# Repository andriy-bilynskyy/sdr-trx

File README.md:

# SDR transceiver

## General info

- [SDR wiki](https://en.wikipedia.org/wiki/Software-defined_radio)
- [Quadrature Mixers, IQ Demodulation, and the Tayloe Detector](https://www.youtube.com/watch?v=JuuKF1RFvBM)
- [A Software-Defined Radio for the Masses, Part 1](https://www.arrl.org/files/file/Technology/tis/info/pdf/020708qex013.pdf)
- [Hardware Implementation of Software Radio Receivers](https://www.ripublication.com/irph/ijeee_spl/ijeeev7n4_08.pdf)

## Main concept

- Fully open source design include HW and SW
- Only free development SW
- Single board design to keep design simple
- SMT design
- Standalone battery powered device

## Folder structure

- **schematic/** - KiCad PCB design. Schematic, PCB routing, manufacture documentation.
- **simulation/** - HW components spice simulations.
- **firmware/** - firmware.
- **calculations/** - calculations and considerations needed for HW/SW design implementation.
- **datasheets/** - datasheets used during design implementations.
- **tests/** - projects to check design components functionality.

## Block diagram

See schematic/sdr-trx/sdr-trx.sch which is top level schematic.

## Great thanks for sharing their approaches knowledges and considerations

- M0NKA http://www.m0nka.co.uk/ - Small and inexpensive homebrew HF radio.
- https://www.flexradio.com/ - RF transceivers.
- https://elecraft.com/products/kx3-all-mode-160-6-m-transceiver - SDR transceiver.
- IN3OTD https://www.qsl.net/in3otd/index.html - lot of very useful information information and approaches. RF PA got from this site.
- https://ludens.cl/Electron/Electron.html - Here's the best explanation of common mistake in push-pull RF PA transformers design I've ever seen. See https://ludens.cl/Electron/mosfetamps/amps.html.
- https://www.youtube.com/watch?v=byF1FLdbUiA - Simple and understandable explanation of a directional coupler.
- https://rf-tools.com/lc-filter/ - Perfect on-line filter calculator.

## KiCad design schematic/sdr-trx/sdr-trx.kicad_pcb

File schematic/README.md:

# SDR transceiver schematic

## Folder structure

- **sdr-trx/** - KiCad PCB project, [KiCad](https://kicad-pcb.org/).  The folder contains schematics and PCB routing. Used KiCad version 5.1.5. Standard KiCad libraries are involved, so please check your version if you have troubles with standard components.
- **mcu-pinout.ioc** - STM32 MCU pinout. [STM32CubeMX](https://www.st.com/en/development-tools/stm32cubemx.html). Used version 5.6.1.
- **pa-transformer.odg** - RF power amplifier push-pull transformer winding. LibreOffice Draw document. Used version 6.4.3.2.
- **swr-transformer.odg** - SWR meter transformer winding. LibreOffice Draw document. Used version 6.4.3.2.
- **doc/** - generated schematic/PCB documentation extracted from KiCad. Folder containing manufacturing documents. [PCB Manufacturing](https://www.elecrow.com/pcb-manufacturing.html)

## Main features

- Single board design, size 239 x 145 mm.
- Only SMD components are used. Avoid using components with pins under package (BGA, QFN, PLCC) due difficulties during hand soldering. Same situation with components with huge pins count.
- Avoid manual inductors/transformer winding. Only two components need manual winding (PA transformer and SWR meter directional coupler).
- Four sides PCB for better EMI. Shield for low power RF part to avoid influence from MCU and UI digital part.
- No chassis mounted components to avoid using wired connections which are not reliable at lest during development stage.
- Switching DC-DC are not used to decrease their EMI on RF part.
- Reduced mechanical buttons due to using capacitive touchscreen.
- On-board Li-batteries. Batteries protection and cell balancing are used.
- Flexible power management. MCU controls powering of RF circuit.
- Covers all HF bands 1.8 - 30 MHz.
- 5W RF power amplifies. Compromise between PCB size and transmitted power. MCU controls the temperature of output RF LDMOS transistors. Output power is also MCU controlled.
- On-board SWR meter. Specialized detector IC is used to increase accuracy.
- Input power supply and ESD protection on inputs.
- Low harmonic distortion due to direct conversion and 2 stages filtration (5-th order Chebyshev BPF after modulator and 7-th order Elliptic LPF after power amplifier).
- Low noise RF-receiver.
- On-board audio amplifier to use cheap headsets for PC.
- USB OTG and SD card interface.

## Known HW issues rev v1.0

See doc/hw_issues.odt

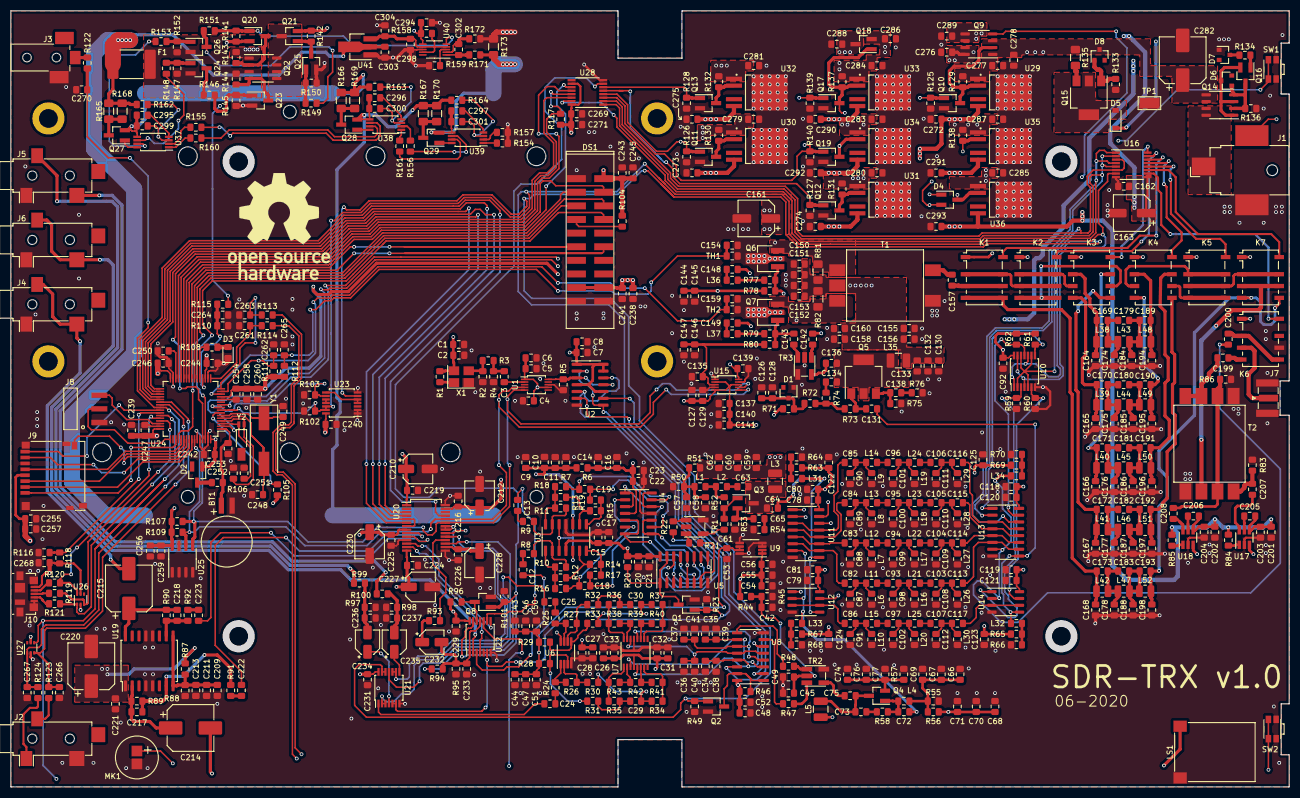
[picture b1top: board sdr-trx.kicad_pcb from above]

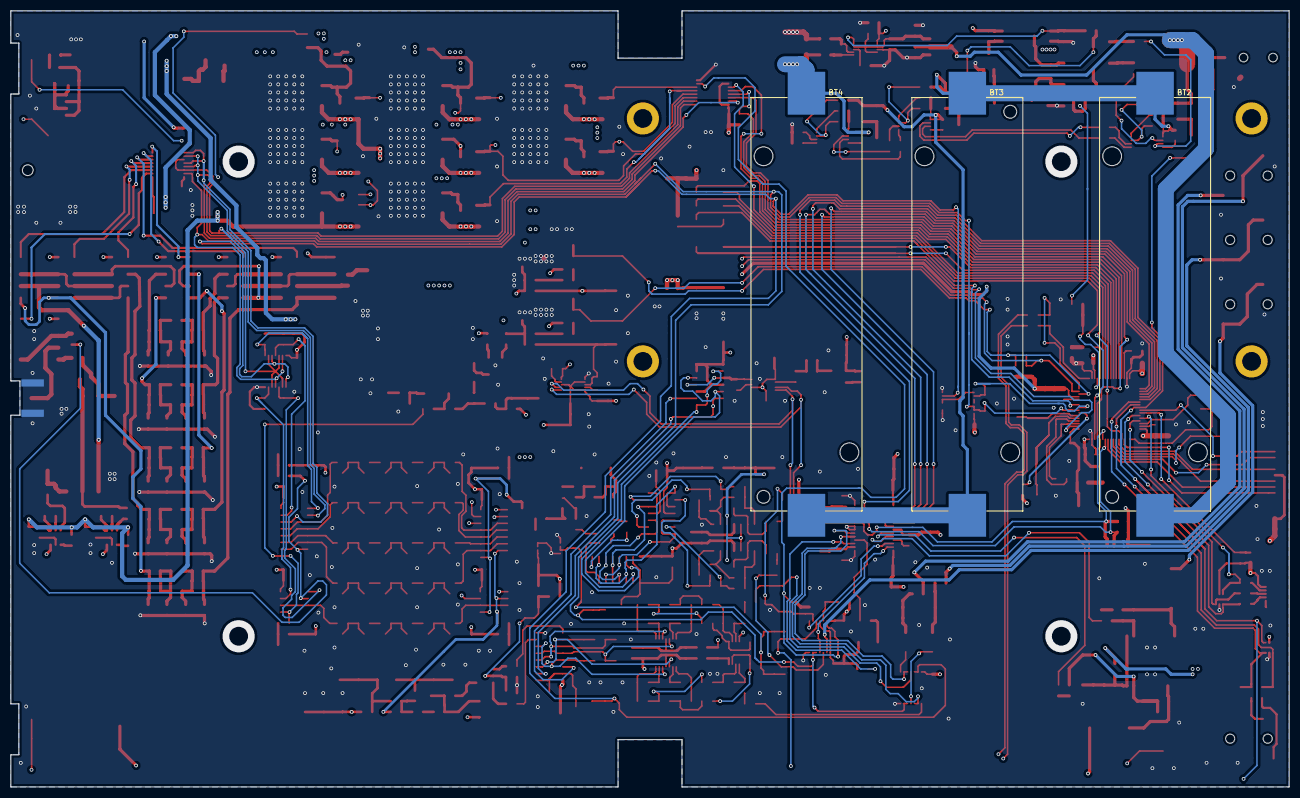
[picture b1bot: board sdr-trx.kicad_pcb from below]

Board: 4 copper layers, 238.4 x 144.7 mm, 645 parts (3 on the bottom side), 372 nets.

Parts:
BT1: ML-920S; ML920S
BT2, BT3, BT4: 18650-holder-1042; BATT-18650-1042
C1, C3, C4, C5, C8, C10, C15, C16, C20, C22, C27, C32, C45, C46, C47, C48, C56, C57, C59, C61, C63, C64, C65, C66, C68, C72, C73, C74, C75, C80, C81, C82, C83, C84, C85, C86, C92, C113, C114, C115, C116, C117, C118, C119, C122, C123, C124, C125, C128, C129, C131, C132, C134, C135, C136, C138, C139, C140, C142, C143, C144, C146, C148, C149, C150, C151, C152, C153, C154, C157, C159, C199, C200, C201, C202, C205, C206, C207, C208, C211, C216, C219, C221, C224, C225, C226, C229, C231, C240, C241, C243, C244, C246, C247, C253, C255, C258, C259, C261, C262, C263, C264, C265, C269, C277, C278, C279, C280, C281, C283, C284, C285, C286, C287, C298, C299, C300, C301, C302, C303, C304: 0.1uF; C_0805_2012Metric_Pad1.15x1.40mm_HandSolder
C2, C7, C11, C14, C21, C28, C33, C49, C50, C51, C52, C54, C58, C60, C67, C70, C76, C78, C79, C120, C121, C133, C137, C145, C147, C203, C204, C213, C254, C294, C295, C296, C297: 10nF; C_0805_2012Metric_Pad1.15x1.40mm_HandSolder
C6, C9, C12, C13, C17, C23, C24, C25, C26, C31, C42, C43, C44, C53, C55, C126, C127, C130, C141, C155, C156, C158, C160, C162, C209, C222, C223, C242: 1.0uF; C_0805_2012Metric_Pad1.15x1.40mm_HandSolder
C18, C19, C29, C30, C38, C39, C40, C41: 8.2nF 1%; C_0805_2012Metric_Pad1.15x1.40mm_HandSolder
C34, C35, C36, C37: N/A; C_0805_2012Metric_Pad1.15x1.40mm_HandSolder
C62, C69, C71, C77, C89, C110, C179, C194, C217, C218, C266, C267, C270: 1.0nF; C_0805_2012Metric_Pad1.15x1.40mm_HandSolder
C87: 3.3nF; C_0805_2012Metric_Pad1.15x1.40mm_HandSolder
C88, C109, C174: 1.8nF; C_0805_2012Metric_Pad1.15x1.40mm_HandSolder
C90, C111, C195: 560pF; C_0805_2012Metric_Pad1.15x1.40mm_HandSolder
C91, C112: 300pF; C_0805_2012Metric_Pad1.15x1.40mm_HandSolder
C93, C103, C180: 620pF; C_0805_2012Metric_Pad1.15x1.40mm_HandSolder
C94, C104, C196: 330pF; C_0805_2012Metric_Pad1.15x1.40mm_HandSolder
C95, C105, C182: 200pF; C_0805_2012Metric_Pad1.15x1.40mm_HandSolder
C96, C106, C183: 91pF; C_0805_2012Metric_Pad1.15x1.40mm_HandSolder
C97, C107: 62pF; C_0805_2012Metric_Pad1.15x1.40mm_HandSolder
C98: 4.7nF; C_0805_2012Metric_Pad1.15x1.40mm_HandSolder
C99: 2.7nF; C_0805_2012Metric_Pad1.15x1.40mm_HandSolder
C100: 1.5nF; C_0805_2012Metric_Pad1.15x1.40mm_HandSolder
C101, C175: 910pF; C_0805_2012Metric_Pad1.15x1.40mm_HandSolder
C102, C176: 510pF; C_0805_2012Metric_Pad1.15x1.40mm_HandSolder
C108: 3.0nF; C_0805_2012Metric_Pad1.15x1.40mm_HandSolder
C161, C163: 47uF 16V; CP_Elec_6.3x5.8
C164: 1.6nF; C_0805_2012Metric_Pad1.15x1.40mm_HandSolder
C165, C185, C189: 750pF; C_0805_2012Metric_Pad1.15x1.40mm_HandSolder
C166, C186, C190: 430pF; C_0805_2012Metric_Pad1.15x1.40mm_HandSolder
C167, C187, C191: 240pF; C_0805_2012Metric_Pad1.15x1.40mm_HandSolder
C168: 130pF; C_0805_2012Metric_Pad1.15x1.40mm_HandSolder
C169, C233, C236, C237: 220pF; C_0805_2012Metric_Pad1.15x1.40mm_HandSolder
C170: 120pF; C_0805_2012Metric_Pad1.15x1.40mm_HandSolder
C171, C193: 68pF; C_0805_2012Metric_Pad1.15x1.40mm_HandSolder
C172: 39pF; C_0805_2012Metric_Pad1.15x1.40mm_HandSolder
C173: 18pF; C_0805_2012Metric_Pad1.15x1.40mm_HandSolder
C177: 270pF; C_0805_2012Metric_Pad1.15x1.40mm_HandSolder
C178, C192: 160pF; C_0805_2012Metric_Pad1.15x1.40mm_HandSolder
C181: 360pF; C_0805_2012Metric_Pad1.15x1.40mm_HandSolder
C184: 1.3nF; C_0805_2012Metric_Pad1.15x1.40mm_HandSolder
C188: 150pF; C_0805_2012Metric_Pad1.15x1.40mm_HandSolder
C197: 180pF; C_0805_2012Metric_Pad1.15x1.40mm_HandSolder
C198: 110pF; C_0805_2012Metric_Pad1.15x1.40mm_HandSolder
C210, C212, C227, C228, C230: 10uF 35V; CP_Elec_5x5.8
C214, C215, C220, C282: 330uF 16V; CP_Elec_8x10.5
C232, C234, C235: 1.0uF 50V; CP_Elec_4x5.4
C238, C239, C245, C250, C256, C257, C260, C268, C271, C272, C273, C274, C275, C276, C288, C289, C290, C291, C292, C293: 4.7uF; C_0805_2012Metric_Pad1.15x1.40mm_HandSolder
C248, C249, C251, C252: 22pF; C_0805_2012Metric_Pad1.15x1.40mm_HandSolder
D1: BZX84-C4V7; D_SOT-23_ANK
D2: BAT54W; SOT-23_Handsoldering
D3: 150080RS75000; D_0805_2012Metric_Pad1.15x1.40mm_HandSolder
D4: BAT54AW; SOT-23_Handsoldering
D5: PMEG2010ER; D_SOD-123
D6, D7: BZX84-C12; D_SOT-23_ANK
D8: BZX84-C2V4; D_SOT-23_ANK
DS1: NHD-4.3-480272FT-CTXL-CTP
F1: ASMDC300F/24; Fuse_2920_7451Metric_Pad2.10x5.45mm_HandSolder
J1: PJ-036AH-SMT; BarrelJack_CUI_PJ-036AH-SMT_Horizontal
J2: SJ-3524-SMT-TR; Jack_3.5mm_CUI_SJ-3524-SMT_Horizontal
J3: PJ1-022-SMT
J4: SJ-3524-SMT-TR-GR; Jack_3.5mm_CUI_SJ-3524-SMT_Horizontal
J5: SJ-3524-SMT-TR-BE; Jack_3.5mm_CUI_SJ-3524-SMT_Horizontal
J6: SJ-3524-SMT-TR-PI; Jack_3.5mm_CUI_SJ-3524-SMT_Horizontal
J7: CON-SMA-EDGE; SMA_Samtec_SMA-J-P-X-ST-EM1_EdgeMount
J8: TSM-103-02
J9: DM3D-SF; microSD_HC_Hirose_DM3D-SF
J10: 47346-0001; USB_Micro-B_Molex_47346-0001
K1, K2, K3, K4, K5, K6, K7: AGQ200A12; Relay_DPDT_Omron_G6K-2F-Y
L1, L4, L31, L32, L33, L34: MLZ2012N101LT000; L_0805_2012Metric_Pad1.15x1.40mm_HandSolder
L2: MLF2012DR22; L_0805_2012Metric_Pad1.15x1.40mm_HandSolder
L3, L5, L35: LQW32FT470M0HL; L_1210_3225Metric_Pad1.42x2.65mm_HandSolder
L6, L14, L24, L26: MLF2012A1R5; L_0805_2012Metric_Pad1.15x1.40mm_HandSolder
L7, L15, L25, L27: MLF2012DR82; L_0805_2012Metric_Pad1.15x1.40mm_HandSolder
L8, L28: MLF2012DR47; L_0805_2012Metric_Pad1.15x1.40mm_HandSolder
L9, L29: MLF2012DR27; L_0805_2012Metric_Pad1.15x1.40mm_HandSolder
L10, L30: MLF2012DR15; L_0805_2012Metric_Pad1.15x1.40mm_HandSolder
L11, L21: MLF2012E6R8; L_0805_2012Metric_Pad1.15x1.40mm_HandSolder
L12, L22: MLF2012A3R9; L_0805_2012Metric_Pad1.15x1.40mm_HandSolder
L13, L23: MLF2012A2R2; L_0805_2012Metric_Pad1.15x1.40mm_HandSolder
L16, L36, L37: MLF2012A1R0; L_0805_2012Metric_Pad1.15x1.40mm_HandSolder
L17: MLF2012DR56; L_0805_2012Metric_Pad1.15x1.40mm_HandSolder
L18: MLF2012DR33; L_0805_2012Metric_Pad1.15x1.40mm_HandSolder
L19: MLF2012DR18; L_0805_2012Metric_Pad1.15x1.40mm_HandSolder
L20: MLF2012DR10; L_0805_2012Metric_Pad1.15x1.40mm_HandSolder
L38: 744758327A; L_1008_2520Metric
L39: 744758315A; L_1008_2520Metric
L40, L44: 744758310A; L_1008_2520Metric
L41, L45: 744758256A; L_1008_2520Metric
L42, L46, L51: 744762233A; L_1008_2520Metric
L43, L48: 744758318A; L_1008_2520Metric
L47, L52: 744762222A; L_1008_2520Metric
L49: 744758312A; L_1008_2520Metric
L50: 744758268A; L_1008_2520Metric
LS1: CMS-15113-078SP; CMS-15113-078S
MK1: DOM-3027L-HD-R
Q1, Q2, Q8, Q10, Q11, Q12, Q13, Q17, Q19, Q27, Q28, Q29: BSS138P; SOT-23_Handsoldering
Q3: MMBT2222A; SOT-23_Handsoldering
Q4: BFU520W; SOT-23_Handsoldering
Q5: DZT2222A; SOT-223-3_TabPin2
Q6, Q7: PD85004; SOT-89-3_Handsoldering
Q9, Q14, Q22: Si4909DY; SO-8_3.9x4.9mm_P1.27mm
Q15: BCP52; SOT-223-3_TabPin2
Q16, Q24, Q26: 2SB1198K; SOT-23_Handsoldering
Q18, Q21: DMP3099L; SOT-23_Handsoldering
Q20, Q23, Q25: 2SC2412K; SOT-23_Handsoldering
R1, R20, R46, R59, R60, R61, R62, R63, R64, R65, R66, R67, R68, R69, R70, R84, R85, R96, R134, R136: 10K; R_0805_2012Metric_Pad1.15x1.40mm_HandSolder
R2, R4, R21, R22: 100R; R_0805_2012Metric_Pad1.15x1.40mm_HandSolder
R3, R83, R86: 68R; R_0805_2012Metric_Pad1.15x1.40mm_HandSolder
R5: 51R; R_0805_2012Metric_Pad1.15x1.40mm_HandSolder
R6, R7, R26, R27, R28, R29, R38, R40, R41, R43, R44, R45, R87, R88: 1K 1%; R_0805_2012Metric_Pad1.15x1.40mm_HandSolder
R8, R9, R10, R11, R12, R13, R14, R15, R110, R111, R112: 10K 1%; R_0805_2012Metric_Pad1.15x1.40mm_HandSolder
R16, R17, R18, R19, R34, R35, R36, R37, R47, R48: 100R 1%; R_0805_2012Metric_Pad1.15x1.40mm_HandSolder
R23, R49, R95, R101, R102, R103, R104, R105, R117, R118, R125, R126, R127, R128, R139, R140: 47K; R_0805_2012Metric_Pad1.15x1.40mm_HandSolder
R24, R25, R76, R119, R120, R121, R122, R123, R124: 22R; R_0805_2012Metric_Pad1.15x1.40mm_HandSolder
R30, R31, R32, R33: 820R 1%; R_0805_2012Metric_Pad1.15x1.40mm_HandSolder
R39, R42: 10R 1%; R_0805_2012Metric_Pad1.15x1.40mm_HandSolder
R50, R55, R94: 2.2K; R_0805_2012Metric_Pad1.15x1.40mm_HandSolder
R51, R71, R78, R80: 1.8K; R_0805_2012Metric_Pad1.15x1.40mm_HandSolder
R52: 180R; R_0805_2012Metric_Pad1.15x1.40mm_HandSolder
R53, R75: 47R; R_0805_2012Metric_Pad1.15x1.40mm_HandSolder
R54: 18R; R_0805_2012Metric_Pad1.15x1.40mm_HandSolder
R56, R91, R92, R97, R98, R99, R100, R129, R130, R131, R132, R133, R137, R138: 4.3K; R_0805_2012Metric_Pad1.15x1.40mm_HandSolder
R57: 150R; R_0805_2012Metric_Pad1.15x1.40mm_HandSolder
R58, R162, R163, R164, R171, R172: 470R; R_0805_2012Metric_Pad1.15x1.40mm_HandSolder
R72: 15K; R_0805_2012Metric_Pad1.15x1.40mm_HandSolder
R73: 160R; R_0805_2012Metric_Pad1.15x1.40mm_HandSolder
R74: 4.7R; R_0805_2012Metric_Pad1.15x1.40mm_HandSolder
R77, R79, R107, R109, R154, R155, R156, R157, R160, R161: 1K; R_0805_2012Metric_Pad1.15x1.40mm_HandSolder
R81, R82: 100R 0.5W; R_1206_3216Metric_Pad1.42x1.75mm_HandSolder
R89: 8.2K; R_0805_2012Metric_Pad1.15x1.40mm_HandSolder
R90: 6.8K; R_0805_2012Metric_Pad1.15x1.40mm_HandSolder
R93: 0R; R_0805_2012Metric_Pad1.15x1.40mm_HandSolder
R106, R108, R113, R114: 390R; R_0805_2012Metric_Pad1.15x1.40mm_HandSolder
R115: 36K 1%; R_0805_2012Metric_Pad1.15x1.40mm_HandSolder
R116: 68K; R_0805_2012Metric_Pad1.15x1.40mm_HandSolder
R135: 15R 0.25W; R_1206_3216Metric_Pad1.42x1.75mm_HandSolder
R141, R142, R143, R144, R145, R147, R150, R152: 1M; R_0805_2012Metric_Pad1.15x1.40mm_HandSolder
R146, R149, R151: 4.7M; R_0805_2012Metric_Pad1.15x1.40mm_HandSolder
R148, R153, R158: 510K; R_0805_2012Metric_Pad1.15x1.40mm_HandSolder
R159: 3K 1%; R_0805_2012Metric_Pad1.15x1.40mm_HandSolder
R165, R166, R167, R168, R169, R170: 75R 0.25W; R_1206_3216Metric_Pad1.42x1.75mm_HandSolder
R173: 20mR 0.25W 1%; R_1206_3216Metric_Pad1.42x1.75mm_HandSolder
SW1, SW2: EVQP7A; SW_SPST_EVQP7A
T1: BN43-202; BN-43-202-5P
T2: BN43-202; BN43-202-8P
TH1, TH2: CMFB3435103; R_0805_2012Metric_Pad1.15x1.40mm_HandSolder
TP1: 5019; TestPoint_Keystone_5019_Minature
TR1, TR2, TR3: CX2047LANL
U1: Si5351A-B-GT; MSOP-10_3x3mm_P0.5mm
U2: PO74G74A; SOIC-14_3.9x8.7mm_P1.27mm
U3: AD8604; SOIC-14_3.9x8.7mm_P1.27mm
U4: AD8618; SOIC-14_3.9x8.7mm_P1.27mm
U5, U8, U11, U13: SN74CBT3253C; SOIC-16_3.9x9.9mm_P1.27mm
U6: LT6237; MSOP-8_3x3mm_P0.65mm
U7: LT6238; SSOP-16_3.9x4.9mm_P0.635mm
U9: LTC6655CHMS8-2.5; MSOP-8_3x3mm_P0.65mm
U10: SN74HC126P; TSSOP-14_4.4x5mm_P0.65mm
U12, U14: SN74CBT3305C; SO-8_3.9x4.9mm_P1.27mm
U15: AD5243BRMZ; MSOP-10_3x3mm_P0.5mm
U16: ULN2003V12T16-13; TSSOP-16_4.4x5mm_P0.65mm
U17, U18: LTC5507; SOT-23-6_Handsoldering
U19: TCA0372BDW; SOIC-16W_7.5x10.3mm_P1.27mm
U20: WM8731; SSOP-28_5.3x10.2mm_P0.65mm
U21, U22: 74HC4066PW; TSSOP-14_4.4x5mm_P0.65mm
U23: SN74HC00P; TSSOP-14_4.4x5mm_P0.65mm
U24: STM32F413RHTx; LQFP-64_10x10mm_P0.5mm
U25: M24C64-RDW; SOIC-8_3.9x4.9mm_P1.27mm
U26, U27: NUP4202; SOT-363_SC-70-6
U28: SN74HC595P; TSSOP-16_4.4x5mm_P0.65mm
U29, U30, U31, U32, U33: LF50ABPT; PPAK
U34, U35, U36: LF33CPT; PPAK
U37, U38, U39: S-8209A; TSSOP-8_4.4x3mm_P0.65mm
U40: INA300; VSSOP-10_3x3mm_P0.5mm
U41: S-812C50A; SOT-89-3_Handsoldering
X1: ASTX-H11-27.000MHZ; Oscillator_SMD_Abracon_ASE-4Pin_3.2x2.5mm_HandSoldering
Y1: J49SML-A-G-G-K-24M0; Crystal_SMD_HC49-SD
Y2: MS3V-T1R-32.768KHZ-12.5PF; Crystal_SMD_MicroCrystal_MS3V-T1R

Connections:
+3.3V: C92.1, C210.1, C212.1, C216.1, C219.1, C229.1, C231.1, C239.1, C240.1, C242.1, C243.1, C244.1, C245.1, C246.1, C247.1, C255.1, C256.1, C257.1, C259.1, C269.1, C271.1, C291.1, D2.1, DS1.1, J9.4, R61.2, R62.2, R96.2, R104.2, R105.1, R107.1, R109.1, R117.2, U10.14, U20.1, U20.27, U21.14, U22.14, U23.14, U24.19, U24.32, U24.48, U24.64, U25.8, U27.5, U28.10, U28.16, U35.5
+3.3V-RF: C1.1, C2.1, C4.1, C5.1, C6.1, C7.1, C8.1, C292.1, R1.1, U1.1, U1.7, U2.1, U2.4, U2.10, U2.13, U2.14, U34.5, X1.4
+3.3VA: C201.1, C202.1, C203.1, C204.1, C205.1, C206.1, C224.1, C225.1, C227.1, C230.1, C254.1, C258.1, C260.1, C293.1, R84.1, R85.1, R111.1, R112.1, U17.4, U18.4, U20.8, U20.14, U24.13, U36.5
+5.0V-BL: C238.1, C241.1, C274.1, DS1.17, DS1.18, U31.5
+5.0V-RF: C78.1, C79.1, C80.1, C81.1, C118.1, C119.1, C120.1, C121.1, C122.1, C123.1, C124.1, C125.1, C290.1, R63.2, R65.2, R67.2, R69.2, U11.16, U12.8, U13.16, U14.8, U33.5
+5.0V-RX: C26.1, C27.1, C28.1, C31.1, C32.1, C33.1, C48.1, C52.1, C54.1, C55.1, C56.1, C68.1, C70.1, C71.1, C273.1, L5.1, R44.1, R46.1, R56.1, U6.8, U7.4, U8.16, U9.1, U9.2, U30.5
+5.0V-TX: C14.1, C15.1, C16.1, C17.1, C20.1, C21.1, C22.1, C23.1, C59.1, C60.1, C62.1, C127.1, C129.1, C137.1, C140.1, C141.1, C272.1, L3.1, R6.1, R20.1, R51.1, U3.4, U4.4, U5.16, U15.2, U15.5, U15.8, U29.5
+5.0V-USB: C268.2, C275.1, J10.1, R118.2, U26.5, U32.5
+12V: C220.1, C221.1, C289.1, Q9.5, Q9.6, R87.1, U19.1
+12V-RF: C162.1, C163.1, C288.1, K1.1, K2.1, K3.1, K4.1, K5.1, K6.1, K7.1, Q18.3, U16.9
+12V-TX: C130.1, C132.1, C133.1, C150.2, C151.2, C152.2, C153.2, C155.1, C156.1, C158.1, C160.1, C161.1, C276.1, L35.1, Q9.7, Q9.8, R71.1, R81.2, R82.2, T1.2
/BPF/B2#RX: R61.1, U10.8, U11.1, U13.1
/BPF/B2#TX: R62.1, U10.11, U11.15, U13.15
/BPF/B2RX: R59.1, U10.3, U12.1, U14.1
/BPF/B2TX: R60.1, U10.6, U12.7, U14.7
/BPF/BAND0: U11.14, U13.14, U16.1, U16.4, U28.15
/BPF/BAND1: U11.2, U13.2, U16.2, U16.5, U28.1
/BPF/BAND2: U10.2, U10.5, U10.9, U10.12, U16.3, U16.6, U28.2
/BPF/RX-EN: Q2.1, R49.1, U10.1, U10.10, U21.12, U21.13, U23.6
/BPF/RX-IN: C200.2, L34.2, U13.7, U14.2
/BPF/TX-EN: Q1.1, R23.1, R102.2, U10.4, U10.13, U16.7, U21.5, U21.6, U22.5, U22.6, U23.12, U23.13, U24.8
/Battery/+5V: C298.1, C304.1, R158.2, U40.4, U40.7, U40.9, U41.3
/Battery/BAT-A: D5.1, Q21.2, R142.1
/Battery/~UNPLUG: C294.1, J1.3, R158.1, U40.6
/Codec/BIAS: C209.1, C211.1, C213.1, R87.2, R88.1, U19.8, U19.9
/Codec/EXT-MIC: Q8.1, R101.1, U22.13, U28.7
/Codec/HP: C215.2, J4.R, J4.T
/Codec/INP-I: C24.1, U21.1
/Codec/INP-Q: C25.1, U21.11
/Codec/LIN-L: J5.T, R100.1
/Codec/LIN-R: J5.R, R99.1
/Codec/LRCK: U20.5, U20.7, U24.33
/Codec/MCLK: U20.25, U24.37
/Codec/MIC: J6.R, J6.T, U22.2
/Codec/SCL: R109.2, U1.4, U15.6, U20.24, U24.58, U25.6
/Codec/SCLK: U20.3, U24.34
/Codec/SD: U20.4, U24.36
/Codec/SDA: R107.2, U1.5, U15.7, U20.23, U24.59, U25.5
/Codec/SDEXT: U20.6, U24.35
/Detector/BIAS: C43.1, C44.1, C46.1, C47.1, C50.1, C51.1, C53.1, R28.1, R29.1, U9.6, U9.7
/Detector/F00: U2.9, U8.14
/Detector/F90: U2.6, U8.2
/Detector/INP-000: C34.1, C38.1, U7.5, U8.6, U8.13
/Detector/INP-090: C36.1, C40.1, U7.14, U8.5, U8.12
/Detector/INP-180: C35.2, C39.2, U7.3, U8.3, U8.10
/Detector/INP-270: C37.2, C41.2, U7.12, U8.4, U8.11
/Detector/OFFS: C42.1, C45.1, C49.1, R44.2, R45.1, TR2.2
/LNA/IN: C72.1, L33.2, U11.7, U12.2
/LNA/OUT: C75.2, TR2.6
/LPF/ANT: J7.1, K6.3
/LPF/B0IREL: K3.8, U16.16
/LPF/B0OREL: K4.8, U16.13
/LPF/B1IREL: K2.8, U16.15
/LPF/B2IREL: K1.8, U16.14
/LPF/B2OREL: K7.8, U16.11
/LPF/B10REL: K5.8, U16.12
/LPF/TXREL: K6.8, U16.10
/MCU/BAT: C277.1, C278.1, C279.1, C280.1, C281.1, C282.1, C283.1, C284.1, C285.1, C286.1, C287.1, D8.1, Q9.1, Q9.3, Q14.5, Q14.6, Q18.2, Q22.1, R115.2, R129.1, R130.1, R131.1, R132.1, R135.1, R137.1, R138.1, R143.1, U29.1, U30.1, U31.1, U32.1, U33.1, U34.1, U35.1, U36.1
/MCU/BL-PWR: Q12.1, R127.1, U28.5
/MCU/DAH: C266.1, R123.1, U24.38, U27.3
/MCU/DIT: C267.1, R124.1, U24.39, U27.1
/MCU/EXT-CLK: U24.26, U28.11
/MCU/EXT-DATA: U24.61, U28.14
/MCU/EXT-EN#: R117.1, U24.29, U28.13
/MCU/EXT-LAT: U24.28, U28.12
/MCU/FWD: R113.2, U18.3
/MCU/P-DAH: J2.R, R123.2
/MCU/P-DIT: J2.S, R124.2
/MCU/PTT: J3.1, R122.2
/MCU/PTT-BTN: C270.1, R122.1, SW2.1, U24.40, U27.4
/MCU/PWR-BTN: D4.2, SW1.1, U24.10
/MCU/PWR-HLD: D4.1, U24.2
/MCU/PWR-HOLD: D4.3, Q9.4, R138.2, U35.2, U36.2
/MCU/REV: R114.2, U17.3
/MCU/RX-PWR: Q11.1, Q17.1, R126.1, R139.1, U28.4
/MCU/SD-CK: J9.5, U24.53
/MCU/SD-CMD: J9.3, U24.54
/MCU/SD-D0: J9.7, U24.56
/MCU/SD-D1: J9.8, U24.41
/MCU/SD-D2: J9.1, U24.51
/MCU/SD-D3: J9.2, U24.57
/MCU/SD-DET: J9.9, U24.55
/MCU/SWCLK: J8.2, U24.49
/MCU/SWDIO: J8.3, U24.46
/MCU/TH: C154.1, C265.1, R112.2, TH1.1, U24.14
/MCU/TL: C159.1, C262.1, R111.2, TH2.1, U24.15
/MCU/TX-PWR: Q10.1, Q19.1, R125.1, R140.1, U28.3
/MCU/UI-CLK: DS1.3, U24.27
/MCU/UI-INT: DS1.7, U24.62
/MCU/UI-IO0: DS1.5, U24.22
/MCU/UI-IO1: DS1.4, U24.23
/MCU/UI-IO2: DS1.11, U24.24
/MCU/UI-IO3: DS1.12, U24.25
/MCU/UI-NCS: DS1.6, U24.52
/MCU/USB-DM: R120.1, U24.44, U26.6
/MCU/USB-DP: R119.1, U24.45, U26.3
/MCU/USB-ID: R121.1, U24.43, U26.1
/MCU/USB-PWR: Q13.1, R128.1, U28.6
/MCU/USB-VB: R116.2, R118.1, U24.42
/Modulator/BIAS: C9.1, C10.1, C11.1, R6.2, R7.1, U3.3, U3.5, U3.10, U3.12
/Modulator/F00: U2.2, U2.8, U5.14
/Modulator/F90: U2.5, U2.12, U5.2
/Modulator/I+: C18.1, R16.2, U4.6
/Modulator/I-: C18.2, R17.2, U4.2
/Modulator/INP-I: C12.2, U22.3
/Modulator/INP-Q: C13.2, U22.9
/Modulator/Q+: C19.1, R18.2, U4.13
/Modulator/Q-: C19.2, R19.2, U4.9
/PSU/VIN: J1.1, Q14.7, Q14.8
/Power amplifier/BIASH: C139.2, C144.1, C145.1, R78.2, U15.10
/Power amplifier/BIASL: C135.2, C146.1, C147.1, R80.2, U15.3
/Power amplifier/IN: C131.1, L32.2, U13.9, U14.5
/Power amplifier/OUT: C157.2, K1.3, K1.6
/Preamplifier/IN: C61.1, TR1.6
/Preamplifier/OUT: C64.2, L31.2, U11.9, U12.5
/SWR meter/IN: K7.3, K7.6, T2.2
/SWR meter/OUT: C199.2, T2.7, T2.8
GND: BT1.2, C1.2, C2.2, C4.2, C5.2, C6.2, C7.2, C8.2, C9.2, C10.2, C11.2, C14.2, C15.2, C16.2, C17.2, C20.2, C21.2, C22.2, C23.2, C26.2, C27.2, C28.2, C31.2, C32.2, C33.2, C34.2, C35.1, C36.2, C37.1, C38.2, C39.1, C40.2, C41.1, C42.2, C43.2, C44.2, C45.2, C46.2, C47.2, C48.2, C49.2, C50.2, C51.2, C52.2, C53.2, C54.2, C55.2, C56.2, C57.2, C58.2, C59.2, C60.2, C62.2, C66.2, C67.2, C68.2, C69.2, C70.2, C71.2, C74.2, C76.2, C77.2, C78.2, C79.2, C80.2, C81.2, C87.2, C88.2, C89.2, C90.2, C91.2, C92.2, C98.2, C99.2, C100.2, C101.2, C102.2, C108.2, C109.2, C110.2, C111.2, C112.2, C118.2, C119.2, C120.2, C121.2, C122.2, C123.2, C124.2, C125.2, C126.2, C127.2, C128.2, C129.2, C130.2, C132.2, C133.2, C135.1, C137.2, C139.1, C140.2, C141.2, C144.2, C145.2, C146.2, C147.2, C150.1, C151.1, C152.1, C153.1, C154.2, C155.2, C156.2, C158.2, C159.2, C160.2, C161.2, C162.2, C163.2, C164.2, C165.2, C166.2, C167.2, C168.2, C174.2, C175.2, C176.2, C177.2, C178.2, C184.2, C185.2, C186.2, C187.2, C188.2, C194.2, C195.2, C196.2, C197.2, C198.2, C201.2, C202.2, C203.2, C204.2, C209.2, C210.2, C211.2, C212.2, C213.2, C216.2, C219.2, C220.2, C221.2, C224.2, C225.2, C226.2, C227.2, C228.2, C229.2, C230.2, C231.2, C233.2, C236.2, C237.2, C238.2, C239.2, C240.2, C241.2, C242.2, C243.2, C244.2, C245.2, C246.2, C247.2, C248.2, C249.2, C250.2, C251.1, C252.1, C253.2, C254.2, C255.2, C256.2, C257.2, C258.2, C259.2, C260.2, C261.2, C262.2, C263.2, C264.2, C265.2, C266.2, C267.2, C268.1, C269.2, C270.2, C271.2, C272.2, C273.2, C274.2, C275.2, C276.2, C277.2, C278.2, C279.2, C280.2, C281.2, C282.2, C283.2, C284.2, C285.2, C286.2, C287.2, C288.2, C289.2, C290.2, C291.2, C292.2, C293.2, C294.2, C298.2, C303.2, C304.2, D1.2, D3.1, D7.2, DS1.2, DS1.19, DS1.20, J1.2, J2.T, J3.2, J4.S, J5.S, J6.S, J7.2, J8.1, J9.6, J9.10, J9.11, J10.5, J10.6, K6.6, L6.2, L7.2, L8.2, L9.2, L10.2, L16.2, L17.2, L18.2, L19.2, L20.2, L26.2, L27.2, L28.2, L29.2, L30.2, LS1.1, MK1.1, Q1.2, Q2.2, Q6.2, Q7.2, Q8.2, Q10.2, Q11.2, Q12.2, Q13.2, Q17.2, Q19.2, Q20.2, Q23.2, Q25.2, R2.1, R4.1, R5.1, R7.2, R23.2, R45.2, R49.2, R50.2, R53.2, R54.2, R55.2, R57.2, R59.2, R60.2, R64.2, R66.2, R68.2, R70.2, R75.2, R76.2, R83.2, R86.1, R88.2, R95.2, R97.2, R98.2, R101.2, R102.1, R103.1, R110.2, R116.1, R125.2, R126.2, R127.2, R128.2, R133.2, R136.2, R139.2, R140.2, R141.2, R145.2, R150.2, R154.2, R157.2, R159.1, R172.1, R173.2, SW1.2, SW2.2, T1.4, T2.1, T2.5, TH1.2, TH2.2, TP1.1, TR1.4, TR2.4, TR3.2, TR3.6, U1.8, U2.7, U3.11, U4.11, U5.8, U6.4, U7.13, U8.8, U9.3, U9.4, U9.5, U9.8, U10.7, U11.8, U12.4, U13.8, U14.4, U15.1, U15.4, U15.9, U16.8, U17.2, U18.2, U19.4, U19.5, U19.12, U19.13, U20.11, U20.15, U20.21, U20.22, U20.28, U21.7, U22.7, U23.1, U23.2, U23.7, U24.12, U24.18, U24.31, U24.47, U24.60, U24.63, U25.1, U25.2, U25.3, U25.4, U25.7, U26.2, U27.2, U28.8, U29.3, U30.3, U31.3, U32.3, U33.3, U34.3, U35.3, U36.3, U40.8, U41.1, X1.2
unnamed: BT1.1, C253.1, R106.2, U24.1
unnamed: BT2.1, C303.1, F1.1, R162.1, R165.1, R168.1, U41.2
unnamed: BT2.2, BT3.1, C295.2, C299.2, Q27.2, R163.1, R166.1, R169.1, U37.5
unnamed: BT3.2, BT4.1, C296.2, C300.2, Q28.2, R164.1, R167.1, R170.1, U38.5
unnamed: BT4.2, C297.2, C301.2, Q29.2, R171.1, R173.1, U39.5
unnamed: C3.1, U1.2
unnamed: C3.2, R3.2, R4.2
unnamed: C12.1, R8.1
unnamed: C13.1, R9.1
unnamed: C24.2, R24.1
unnamed: C25.2, R25.1
unnamed: C29.1, R30.2, R34.1
unnamed: C29.2, R31.2, R35.1
unnamed: C30.1, R32.2, R36.1
unnamed: C30.2, R33.2, R37.1
unnamed: C57.1, C58.1, L1.1, R50.1, R51.2
unnamed: C61.2, Q3.1, R52.2
unnamed: C63.1, L2.2
unnamed: C63.2, C64.1, L3.2, Q3.3
unnamed: C65.1, Q3.2, R53.1
unnamed: C65.2, R54.1
unnamed: C66.1, C67.1, C69.1, L4.1, R55.1, R56.2
unnamed: C72.2, L4.2, Q4.1, R58.2
unnamed: C73.1, R58.1
unnamed: C73.2, C75.1, L5.2, Q4.3
unnamed: C74.1, C76.1, C77.1, Q4.2, R57.1
unnamed: C82.1, U11.6, U11.10
unnamed: C82.2, C87.1, L6.1, L11.1
unnamed: C83.1, U11.5, U11.11
unnamed: C83.2, C88.1, L7.1, L12.1
unnamed: C84.1, U11.4, U11.12
unnamed: C84.2, C89.1, L8.1, L13.1
unnamed: C85.1, U11.3, U11.13
unnamed: C85.2, C90.1, L9.1, L14.1
unnamed: C86.1, U12.3, U12.6
unnamed: C86.2, C91.1, L10.1, L15.1
unnamed: C93.1, L11.2
unnamed: C93.2, C98.1, L16.1, L21.1
unnamed: C94.1, L12.2
unnamed: C94.2, C99.1, L17.1, L22.1
unnamed: C95.1, L13.2
unnamed: C96.1, L14.2
unnamed: C97.1, L15.2
unnamed: C95.2, C100.1, L18.1, L23.1
unnamed: C96.2, C101.1, L19.1, L24.1
unnamed: C97.2, C102.1, L20.1, L25.1
unnamed: C103.1, L21.2
unnamed: C103.2, C108.1, C113.1, L26.1
unnamed: C104.1, L22.2
unnamed: C104.2, C109.1, C114.1, L27.1
unnamed: C105.1, L23.2
unnamed: C105.2, C110.1, C115.1, L28.1
unnamed: C106.1, L24.2
unnamed: C106.2, C111.1, C116.1, L29.1
unnamed: C107.1, L25.2
unnamed: C107.2, C112.1, C117.1, L30.1
unnamed: C113.2, U13.6, U13.10
unnamed: C114.2, U13.5, U13.11
unnamed: C115.2, U13.4, U13.12
unnamed: C116.2, U13.3, U13.13
unnamed: C117.2, U14.3, U14.6
unnamed: C126.1, C128.1, D1.1, R71.2, R72.2
unnamed: C131.2, Q5.1, R73.2
unnamed: C134.1, R74.1
unnamed: C134.2, C136.1, L35.2, Q5.2
unnamed: C136.2, TR3.4
unnamed: C138.1, Q5.3, R75.1
unnamed: C138.2, R76.1
unnamed: C142.1, TR3.3
unnamed: C142.2, Q6.1, R77.2, R78.1
unnamed: C143.1, TR3.1
unnamed: C143.2, Q7.1, R79.2, R80.1
unnamed: C148.1, L36.2
unnamed: C148.2, Q6.3, R81.1, T1.1
unnamed: C149.1, L37.2
unnamed: C149.2, Q7.3, R82.1, T1.3
unnamed: C157.1, T1.5
unnamed: C164.1, C169.1, K3.2, L38.1
unnamed: C165.1, C170.1, K3.4, L39.1
unnamed: C166.1, C171.1, K3.7, L40.1
unnamed: C167.1, C172.1, K3.5, L41.1
unnamed: C168.1, C173.1, K1.4, K1.5, L42.1
unnamed: C169.2, C174.1, C179.1, L38.2, L43.1
unnamed: C170.2, C175.1, C180.1, L39.2, L44.1
unnamed: C171.2, C176.1, C181.1, L40.2, L45.1
unnamed: C172.2, C177.1, C182.1, L41.2, L46.1
unnamed: C173.2, C178.1, C183.1, L42.2, L47.1
unnamed: C179.2, C184.1, C189.1, L43.2, L48.1
unnamed: C180.2, C185.1, C190.1, L44.2, L49.1
unnamed: C181.2, C186.1, C191.1, L45.2, L50.1
unnamed: C182.2, C187.1, C192.1, L46.2, L51.1
unnamed: C183.2, C188.1, C193.1, L47.2, L52.1
unnamed: C189.2, C194.1, K4.2, L48.2
unnamed: C190.2, C195.1, K4.4, L49.2
unnamed: C191.2, C196.1, K4.7, L50.2
unnamed: C192.2, C197.1, K4.5, L51.2
unnamed: C193.2, C198.1, K7.4, K7.5, L52.2
unnamed: C199.1, K6.4
unnamed: C200.1, K6.2, K6.5
unnamed: C205.2, U17.5
unnamed: C206.2, U18.5
unnamed: C207.1, U17.6
unnamed: C207.2, R83.1, T2.4
unnamed: C208.1, U18.6
unnamed: C208.2, R86.2, T2.3, T2.6
unnamed: C214.1, C217.1, R89.2, U19.2
unnamed: C214.2, LS1.2
unnamed: C215.1, C218.1, R90.2, U19.16
unnamed: C217.2, R89.1, R91.2, U19.7
unnamed: C218.2, R90.1, R92.2, U19.10
unnamed: C222.1, R91.1
unnamed: C222.2, U20.9
unnamed: C223.1, R92.1
unnamed: C223.2, U20.10
unnamed: C226.1, C228.1, U20.16
unnamed: C232.1, R93.1
unnamed: C232.2, C233.1, R94.1, R95.1, U22.1, U22.11
unnamed: C234.1, U21.4
unnamed: C234.2, C236.1, R97.1, R99.2
unnamed: C235.1, U21.8
unnamed: C235.2, C237.1, R98.1, R100.2
unnamed: C248.1, U24.5, Y1.2
unnamed: C249.1, U24.6, Y1.1
unnamed: C250.1, U24.30
unnamed: C251.2, U24.3, Y2.1
unnamed: C252.2, U24.4, Y2.2
unnamed: C261.1, R114.1, U24.17
unnamed: C263.1, R113.1, U24.16
unnamed: C264.1, R110.1, R115.1, U24.20
unnamed: C295.1, U37.4
unnamed: C296.1, U38.4
unnamed: C297.1, U39.4
unnamed: C299.1, R162.2, U37.3
unnamed: C300.1, R163.2, U38.3
unnamed: C301.1, R164.2, U39.3
unnamed: C302.1, R171.2, U40.1
unnamed: C302.2, R172.2, U40.2
unnamed: D2.3, R106.1
unnamed: D3.2, R108.2
unnamed: D5.2, Q15.2
unnamed: D6.1, Q14.1, Q14.3, Q16.2
unnamed: D6.2, Q14.2, Q14.4, Q16.3, R136.1
unnamed: D7.1, R134.2
unnamed: D8.2, Q15.1, R133.1
unnamed: DS1.8, R104.1
unnamed: F1.2, Q22.3, Q24.2, Q26.2, R144.1, R147.1, R152.1
unnamed: J10.2, R120.2
unnamed: J10.3, R119.2
unnamed: J10.4, R121.2
unnamed: K1.2, K1.7, K2.3, K2.6
unnamed: K2.2, K2.7, K3.3
unnamed: K2.4, K2.5, K3.6
unnamed: K4.3, K5.2, K5.7
unnamed: K4.6, K5.4, K5.5
unnamed: K5.3, K5.6, K7.2, K7.7
unnamed: L1.2, L2.1, R52.1
unnamed: L31.1, R63.1, R64.1
unnamed: L32.1, R65.1, R66.1
unnamed: L33.1, R67.1, R68.1
unnamed: L34.1, R69.1, R70.1
unnamed: L36.1, R77.1
unnamed: L37.1, R79.1
unnamed: MK1.2, U22.10
unnamed: Q1.3, R20.2, U5.1, U5.15
unnamed: Q2.3, R46.2, U8.1, U8.15
unnamed: Q8.3, R96.1, U22.12
unnamed: Q9.2, Q10.3, R129.2, U29.2
unnamed: Q11.3, R130.2, U30.2
unnamed: Q12.3, R131.2, U31.2
unnamed: Q13.3, R132.2, U32.2
unnamed: Q15.3, R135.2
unnamed: Q16.1, R134.1
unnamed: Q17.3, Q18.1, Q19.3, R137.2, U33.2, U34.2
unnamed: Q20.1, R141.1, R151.2, U40.5
unnamed: Q20.3, Q22.2, R143.2
unnamed: Q21.1, Q25.3, R142.2
unnamed: Q21.3, Q22.5, Q22.6, Q22.7, Q22.8
unnamed: Q22.4, Q23.3, R144.2
unnamed: Q23.1, R145.1, R146.2
unnamed: Q24.1, R147.2, R148.1
unnamed: Q24.3, R146.1
unnamed: Q25.1, R149.2, R150.1
unnamed: Q26.1, R152.2, R153.1
unnamed: Q26.3, R149.1, R151.1
unnamed: Q27.1, U37.8
unnamed: Q27.3, R165.2, R168.2
unnamed: Q28.1, U38.8
unnamed: Q28.3, R166.2, R169.2
unnamed: Q29.1, U39.8
unnamed: Q29.3, R167.2, R170.2
unnamed: R1.2, X1.1
unnamed: R2.2, R3.1, X1.3
unnamed: R5.2, U1.10, U2.3, U2.11
unnamed: R8.2, R10.1, U3.2
unnamed: R10.2, R12.1, R16.1, U3.1
unnamed: R9.2, R11.1, U3.13
unnamed: R11.2, R13.1, R18.1, U3.14
unnamed: R12.2, R14.1, U3.6
unnamed: R13.2, R15.1, U3.9
unnamed: R14.2, R17.1, U3.7
unnamed: R15.2, R19.1, U3.8
unnamed: R21.1, U5.7
unnamed: R21.2, TR1.1
unnamed: R22.1, U5.9
unnamed: R22.2, TR1.3
unnamed: R24.2, R26.1, U6.1
unnamed: R25.2, R27.1, U6.7
unnamed: R26.2, R30.1, U6.2
unnamed: R27.2, R32.1, U6.6
unnamed: R28.2, R31.1, U6.3
unnamed: R29.2, R33.1, U6.5
unnamed: R34.2, R41.2, U7.7
unnamed: R35.2, R43.1, U7.1
unnamed: R36.2, R38.2, U7.16
unnamed: R37.2, R40.1, U7.10
unnamed: R38.1, R39.2, U7.15
unnamed: R39.1, R40.2, U7.11
unnamed: R41.1, R42.2, U7.6
unnamed: R42.1, R43.2, U7.2
unnamed: R47.1, U8.7
unnamed: R47.2, TR2.1
unnamed: R48.1, U8.9
unnamed: R48.2, TR2.3
unnamed: R72.1, R73.1, R74.2
unnamed: R84.2, U17.1
unnamed: R85.2, U18.1
unnamed: R93.2, U20.18
unnamed: R94.2, U20.17
unnamed: R103.2, U23.9, U24.9
unnamed: R105.2, U24.7
unnamed: R108.1, U24.21
unnamed: R148.2, U37.6
unnamed: R153.2, U37.7
unnamed: R154.1, U39.1
unnamed: R155.1, U37.2
unnamed: R155.2, U38.6
unnamed: R156.1, U38.2
unnamed: R156.2, U39.6
unnamed: R157.1, U39.2
unnamed: R159.2, U40.3
unnamed: R160.1, U37.1
unnamed: R160.2, U38.7
unnamed: R161.1, U38.1
unnamed: R161.2, U39.7
unnamed: U4.1, U4.3, U5.3, U5.10
unnamed: U4.5, U4.7, U5.6, U5.13
unnamed: U4.8, U4.10, U5.4, U5.11
unnamed: U4.12, U4.14, U5.5, U5.12
unnamed: U20.12, U22.8
unnamed: U20.13, U22.4
unnamed: U20.19, U21.2, U21.3
unnamed: U20.20, U21.9, U21.10
unnamed: U23.4, U23.5, U23.8
unnamed: U23.10, U23.11

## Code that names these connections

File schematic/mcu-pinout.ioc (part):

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PA6.Mode=Single Bank 2
PC7.GPIOParameters=GPIO_PuPd,GPIO_Label
Mcu.UserName=STM32F413RHTx
PC10.Signal=SDIO_D2
PC12.Signal=SDIO_CK
PA0.GPIO_Label=V-TH
PC0.GPIOParameters=GPIO_Label
PC0.GPIO_Label=TX_EN
PA11.Mode=OTG/Dual_Role_Device
PA3.GPIOParameters=GPIO_Label
PC5.Mode=Single Bank 2
PC13.GPIO_Label=PWR_HOLD
PB13.Signal=I2S2_CK
PB15.Signal=I2S2_SD
PA2.GPIOParameters=GPIO_Label
RCC.SYSCLKSource=RCC_SYSCLKSOURCE_PLLCLK
PA12.Signal=USB_OTG_FS_DP
PH0\ -\ OSC_IN.Signal=RCC_OSC_IN
PC1.GPIOParameters=GPIO_Label
PB6.Signal=I2C1_SCL
PC7.Signal=GPIO_Input
PB6.Mode=I2C
RCC.HSE_VALUE=24000000
PB2.Signal=GPIO_Output
PB3.GPIO_PuPd=GPIO_PULLUP
PA1.GPIOParameters=GPIO_Label
PB4.Mode=SD_4_bits_Wide_bus
PC14-OSC32_IN.Mode=LSE-External-Oscillator
PA14.Mode=Serial_Wire
PB14.Mode=Full_Duplex_Master
PB5.Mode=SD_4_bits_Wide_bus
PB3.GPIOParameters=GPIO_PuPd,GPIO_Label
PB7.Signal=I2C1_SDA
PA8.Signal=SDIO_D1
PA0.Signal=ADCx_IN0
PC8.GPIOParameters=GPIO_PuPd,GPIO_Label
Mcu.Package=LQFP64
PB9.Signal=GPXTI9
PB1.Signal=QUADSPI_CLK
PA6.Signal=QUADSPI_BK2_IO0
PB12.Mode=Full_Duplex_Master
PA2.GPIO_Label=V-FWD
PA10.Signal=USB_OTG_FS_ID
PB9.GPIO_PuPd=GPIO_PULLUP
PA5.GPIOParameters=GPIO_Label
PC11.Mode=Single Bank 2
PC5.Signal=QUADSPI_BK2_IO3
PB13.Mode=Full_Duplex_Master
PB10.GPIOParameters=GPIO_Label
PA4.GPIO_Label=V-BAT
PC2.GPIO_Label=PWR_BTN
PC4.Mode=Single Bank 2
PB4.Signal=SDIO_D0
PA3.Signal=ADCx_IN3
PB3.GPIO_Label=SDIO_DET
PC15-OSC32_OUT.Mode=LSE-External-Oscillator
PA7.Mode=Single Bank 2
PB9.GPIO_Label=UI-INT
PA10.Mode=OTG/Dual_Role_Device
PC9.GPIO_Label=PTT_BTN
PC11.Signal=QUADSPI_BK2_NCS
PC13.Signal=GPIO_Output
PH1\ -\ OSC_OUT.Mode=HSE-External-Oscillator
PC8.Signal=GPIO_Input
PC2.Signal=GPIO_Input
PC4.Signal=QUADSPI_BK2_IO2
PC6.Signal=I2S2_MCK
PC10.Mode=SD_4_bits_Wide_bus
PC0.Signal=GPIO_Output
PC14-OSC32_IN.Signal=RCC_OSC32_IN
PB9.GPIOParameters=GPIO_PuPd,GPIO_Label
PC8.GPIO_Label=P_DIT
PA13.Signal=SYS_JTMS-SWDIO
PA9.Mode=Activate_VBUS
PH0\ -\ OSC_IN.Mode=HSE-External-Oscillator
PB10.GPIO_Label=SPI5_EN
PC6.Mode=Master_Clock_Activated
PB2.GPIOParameters=GPIO_Label
PA9.Signal=USB_OTG_FS_VBUS
PC7.GPIO_PuPd=GPIO_PULLUP
PC15-OSC32_OUT.Signal=RCC_OSC32_OUT
PA1.Signal=ADCx_IN1
PB10.Signal=GPIO_Output
PB14.Signal=I2S2_ext_SD
PD2.Mode=SD_4_bits_Wide_bus
PA5.Signal=GPIO_Output
PC12.Mode=SD_4_bits_Wide_bus
PB0.Mode=TX_Only_Simplex_Unidirect_Master
PH1\ -\ OSC_OUT.Signal=RCC_OSC_OUT
board=custom
PB15.Mode=Full_Duplex_Master
PC13.GPIOParameters=GPIO_Label
PC2.GPIOParameters=GPIO_PuPd,GPIO_Label
PC1.GPIO_Label=RX_EN
PA1.GPIO_Label=V-TL
PC9.GPIO_PuPd=GPIO_PULLUP
PA4.GPIOParameters=GPIO_Label
PC2.GPIO_PuPd=GPIO_PULLUP
PA13.Mode=Serial_Wire
PC9.GPIOParameters=GPIO_PuPd,GPIO_Label
Mcu.Name=STM32F413R(G-H)Tx
PA2.Signal=ADCx_IN2
PC7.GPIO_Label=P_DAH
PC8.GPIO_PuPd=GPIO_PULLUP
PB3.Signal=GPIO_Input
PA4.Signal=ADCx_IN4
RCC.SYSCLKFreq_VALUE=96000000
PB5.Signal=SDIO_D3
PA12.Mode=OTG/Dual_Role_Device
PA5.GPIO_Label=LED
PA11.Signal=USB_OTG_FS_DM
PB7.Mode=I2C
PA14.Signal=SYS_JTCK-SWCLK
PB2.GPIO_Label=SPI5_LAT
PA0.GPIOParameters=GPIO_Label
PB1.Mode=Single Bank 2
PB8.Mode=TX_Only_Simplex_Unidirect_Master
PB8.Signal=SPI5_MOSI
PA8.Mode=SD_4_bits_Wide_bus
PC9.Signal=GPIO_Input
PD2.Signal=SDIO_CMD
PB0.Signal=SPI5_SCK
PC1.Signal=GPIO_Output
PB12.Signal=I2S2_WS
PA3.GPIO_Label=V-REV
PA7.Signal=QUADSPI_BK2_IO1

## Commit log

2020-03-26 Add clock simulation.
2020-03-27 Add AD9850 demo.
2020-03-27 Extend dds test.
2020-03-28 Add AD9850 driver.
2020-03-28 Add 2 x AD9850 IQ driver.
2020-04-02 Add SSB modulator simulation.
2020-04-02 Add gitignore.
2020-04-03 Add output tx circuit.
2020-04-07 Add detector simulation.
2020-04-07 Improve RX LPF design.
2020-04-08 Reduce opamp noise.
2020-04-09 Use the same capacitors in all LPFs.
2020-04-10 Use 5V VCC.
2020-04-10 Replace impedance transformer.
2020-04-10 Add 3.3V DDS.
2020-04-10 Initial schematic commit.
2020-04-20 Add AD9851 support (6x CLK multiplier).
2020-04-21 Add DCO schematic.
2020-04-21 Add modulator schematic.
2020-04-22 Add project footprint library.
2020-04-22 Update project library.
2020-04-22 Minor schematic cleanup.
2020-04-23 Add LTC6228 SO-8.
2020-04-23 Add detector schematic.
2020-04-23 Improve insamp reference voltage.
2020-04-23 Update schematic - improve insamp reference voltage.
2020-04-25 Add preamplifier schematic.
2020-04-28 Add LNA.
2020-04-28 Use one ground. To be splitted at PCB.
2020-04-29 Add BPF splitting calculations.
2020-05-01 Add BPF (Calculated according https://vpayaem.ru/information6_3.html).
2020-05-03 More accurate LNA simmulation (real inductance).
2020-05-09 Add RF power amplifier simulation.
2020-05-11 Add measurements in LNA.
2020-05-11 Reduce opamp packages.
2020-05-11 Update schematic according to latest simulation.
2020-05-12 Add small size RF amplifier simulation.
2020-05-13 Add preamplifier simulation.
2020-05-13 Add power amplifier schematic.
2020-05-13 Cleanup datasheets.
2020-05-16 Add LPF simulation.
2020-05-16 Update BPF.
2020-05-17 Add LPF schematic. Update BPF schematic.
2020-05-17 Add simple RF power metrics calculator.
2020-05-18 Add SWR meter.
2020-05-19 Update SWR meter.
2020-05-20 Update SWR schematic. Add transformers detailes.
2020-05-24 Add audio codec.
2020-05-27 Add UI unit.
2020-05-31 Add MCU unit schematic.
2020-06-04 Add PSU schematic.
2020-06-05 Add charge CS LPF.
2020-06-05 Schematic annotation and ERC.
2020-06-05 Add missed datasheets.
2020-06-05 Load components into PCB.
2020-06-24 Route PCB.
2020-06-25 Generate PCB documentation.
2020-06-25 Fix shield mask.
2020-06-26 Add README and License.
2020-06-26 Project cleanup.
2020-07-14 Update cross compiler toolchain.
2020-07-17 Extend specification (Add Digikey partnumbers). Minor schematic changes.
2020-07-17 Add digikey order list.
2020-07-21 Add circular buffer library.
2020-07-21 Improve circular buffer interface.
2020-08-01 Add DSP test app.
2020-08-01 Add PCB v1.0 photos.
2020-08-02 Update sdr transmission procedure.
2020-08-02 Minor extensions of sdr transmission procedure.
2020-08-06 Add SDR transceiver test application.
2020-08-27 Fix HW specification.
2020-08-27 Initial FW commit.
2020-08-28 Fix openocd scripts.
2020-08-30 New Makefile structure.
2020-08-30 Formatt sources. Cleanup.
2020-08-30 Extend LED functionality.
2020-08-31 Add board control unit.
2020-08-31 Add transmit/receive control unit.
2020-08-31 Add key unit.
2020-09-16 Add FW (UI unit, Critical errors handler, ...).
2020-09-18 Add RTC.
2020-09-18 Add BKP SRAM API.
2020-09-21 Update RTC unit. - Add LSE failed widget. - Removed setting LSE high drive mode. Durung tests observed LSE startup time ~10S. There is no essential dependency on LSE drive mode.
2020-09-21 Do not wait while qspi write operation complete, run it asynchronous.
2020-09-21 Update hwctl unit (use HW SPI and its interrupt).
2020-09-22 Use standard semaphore interface post/pend in OS dependent implementation.
2020-09-24 ADC dummy implementation with its widget.
2020-09-25 Real ADC implementation.
2020-09-28 Add I2C master driver.
2020-09-28 Minor thread improvements.
2020-09-30 Add RF amplifier driver.
2020-10-02 Add NVRAM driver.
2020-10-05 Avoid code duplication: Introduce common notify widget.
2020-10-05 Try to reinit RTC if LSE fail.
2020-10-10 Minor improve widget date time draw speed.
2020-10-10 Provide errors from rf amplifier to UI.
2020-10-10 Dummy DCO implementation and its widget.
2020-10-10 Fixed i2c one byte reception.
2020-10-14 Read DCO implementation.
2020-10-14 Replace NVRAM IC with FRAM FM24CL64. This brings huge increasing of write performance.
2020-10-14 Minor update RTC interface.
2020-10-18 Add audio codec analog part.
2020-10-18 Add HW issues list.
2020-10-26 Power on-off schematic simulation.
    Power on-off schematic proposed.
    Short press the button to power on.
    Long press the button to power off.
2020-10-29 Add audio codec digital part.
2020-10-29 Make pointer to codec adc buffer const.
2020-10-30 Add different sample rates for audio codec.
2020-11-01 Project cleanup: IRQ, DMA priorities, Makefile fix style target.
2020-11-01 Use UI engine command RAM cache to prevent sending short QSPI transactions. Minor fix in trx widget.
2020-11-01 FreeRTOS integration.
2020-11-01 Implement RTOS critical errors.
2020-11-01 Add HAL FreeRTOS extensions.
2020-11-01 Initial task split.
2020-11-01 Implement RTOS memory management.
2020-11-01 Fix audio click when codec starts. Fix possible crash at realloc.
2020-11-03 Implement dsp task.
2020-11-05 Add UI task events. UI notification from system.
2020-11-06 Introduce application data and its NVRAM storage.
2020-11-07 Add power on/off functionality. Make possible shutdown during notification showing (long press power button). Add battery voltage shutdown and overheat protection.
2020-11-07 Update HW issues list.
2020-11-07 Align buttons in power menu widget.
2020-11-11 Aggregate all RF unit parts into one file. Move all error notifications into one file.
2020-11-11 Add HW PTT button and common transceiver settings widget. Minor improvements.
2020-11-11 Provide application handler to DSP process.
2020-11-12 Lockdown on RF amplifier during reception.
2020-11-12 Add SW version information based on git state.
2020-11-12 Add FW readme.
2020-11-13 Use high level rf unit functions in sensors widget.
2020-11-13 Shut off sound during transmission.
2020-11-14 Fix empty void function declaration f() - f(void).
2020-11-14 Use one IO buffer for audio codec. Create audio sample data type.
2020-11-14 Update CMSIS to version 5.7.0. Sources obtained from https://developer.arm.com/tools-and-software/embedded/cmsis.
2020-11-21 Add SDR simulation PC application.
2020-11-21 Remove no longer needed code to make SW structure more clear.
2020-11-22 Add codec buffer size checker. Fix Makefile.
2020-11-22 Minor schematic fix.
2020-11-22 Spectrum data preparation to UI.
2020-11-22 Make application handler volatile.
2020-11-23 Add RX AGC functionality.
2020-11-24 UI add bitmaps support.
2020-11-25 Dummy spectrum plot.
2020-11-25 Spectrum visualization implementation.
2020-11-25 Fix setting frequency out of valid range.
2020-11-26 Fix LSB USB cases.
2020-11-26 Reduce stack usage.
2020-11-26 Add spectrum plot grid.
2020-11-26 Decrease line width.
2020-11-29 Advanced AGC.
2020-11-29 Updated HW issues list (fix TX buffer opamp).
2020-11-30 Update HW issues.
2020-12-01 Add AM demodulation.
2020-12-01 Improve AM DC offset calculation.
2020-12-03 Sync DSP test framowork with latest firmware.
2020-12-04 Refactoring SDR process.
2020-12-08 Add SDR test process (generate single tone LSB at tuned frequency) to tune RF amplifier and antenna.
2020-12-08 Add TX parameters visible on widget.
2020-12-08 Scale TX output signals to achieve desired transmit power.
2020-12-08 Fix negative SWR reporting. Since measurement circuit accuracy it's possible to have negative SWR value when measured Pr is little bit bigger than Pf actually they are the same.
2020-12-08 Add photos of assembled device.
2020-12-13 RF amplifier LDMOS bias voltage autobalance.
2020-12-30 Update to latest FFTW library.
2020-12-30 Use latest cross compiler version.
